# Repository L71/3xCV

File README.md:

3xCV
====

Eurorack Triple Control Voltage Adder/Attenuator/Inverter

12HP size w panel. 

** work in progress **

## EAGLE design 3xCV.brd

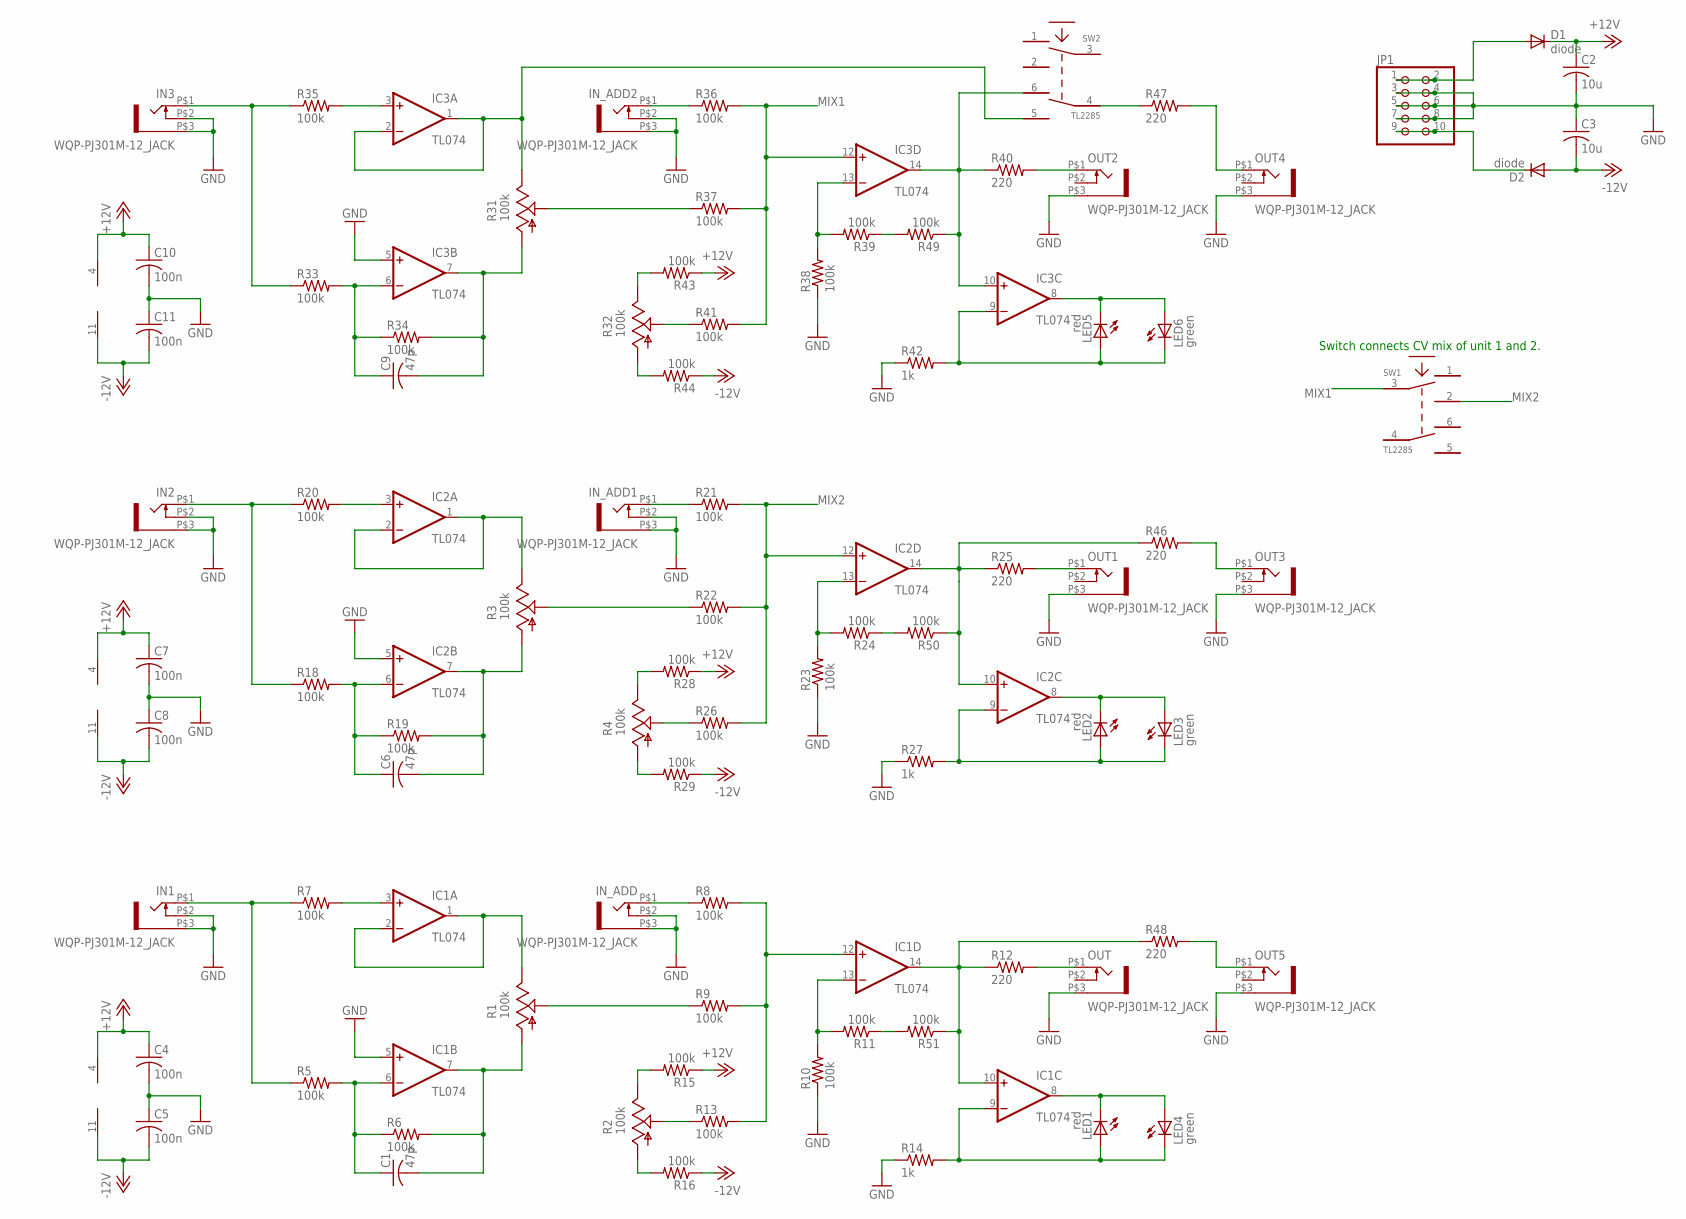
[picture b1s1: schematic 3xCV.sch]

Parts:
C1, C6, C9: 47p; C0603
C2, C3: 10u; C1206
C4, C5, C7, C8, C10, C11: 100n; C0603
D1, D2: diode; DO214AA
IC1, IC2, IC3: TL074; SO14
IN1, IN2, IN3: WQP-PJ301M-12_JACK
IN_ADD, IN_ADD1, IN_ADD2: WQP-PJ301M-12_JACK
JP1: PINHD-2X5; 2X05
LED1, LED2, LED5: red; LED3MM
LED3, LED4, LED6: green; LED3MM
OUT, OUT1, OUT2, OUT3, OUT4, OUT5: WQP-PJ301M-12_JACK
R1, R2, R3, R4, R31, R32: 100k; ALPS_POT_VERTICAL
R5, R6, R7, R8, R9, R10, R11, R13, R15, R16, R18, R19, R20, R21, R22, R23, R24, R26, R28, R29, R33, R34, R35, R36, R37, R38, R39, R41, R43, R44, R49, R50, R51: 100k; R0603
R12, R25, R40, R46, R47, R48: 220; R0603
R14, R27, R42: 1k; R0603
SW1, SW2: TL2285; TL2285_PCB

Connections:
+12V: C2.1, C4.1, C7.1, C10.1, D1.C, IC1.4 (V+), IC2.4 (V+), IC3.4 (V+), R15.1, R28.1, R43.1
-12V: C3.2, C5.2, C8.2, C11.2, D2.A, IC1.11 (V-), IC2.11 (V-), IC3.11 (V-), R16.1, R29.1, R44.1
GND: C2.2, C3.1, C4.2, C5.1, C7.2, C8.1, C10.2, C11.1, IC1.5 (+IN), IC2.5 (+IN), IC3.5 (+IN), IN1.P$2 (3), IN1.P$3 (1), IN2.P$2 (3), IN2.P$3 (1), IN3.P$2 (3), IN3.P$3 (1), IN_ADD.P$2 (3), IN_ADD.P$3 (1), IN_ADD1.P$2 (3), IN_ADD1.P$3 (1), IN_ADD2.P$2 (3), IN_ADD2.P$3 (1), JP1.3, JP1.4, JP1.5, JP1.6, JP1.7, JP1.8, OUT.P$3 (1), OUT1.P$3 (1), OUT2.P$3 (1), OUT3.P$3 (1), OUT4.P$3 (1), OUT5.P$3 (1), R10.1, R14.1, R23.1, R27.1, R38.1, R42.1
MIX1: IC3.12 (+IN), R36.2, R37.2, R41.2, SW1.3
MIX2: IC2.12 (+IN), R21.2, R22.2, R26.2, SW1.2
unnamed: IC1.9 (-IN), LED1.A, LED4.K (C), R14.2
unnamed: IN1.P$1 (2), R5.1, R7.1
unnamed: C1.1, IC1.6 (-IN), R5.2, R6.1
unnamed: IC1.3 (+IN), R7.2
unnamed: IC1.1 (OUT), IC1.2 (-IN), R1.P$1 (E)
unnamed: OUT.P$1 (2), R12.2
unnamed: C1.2, IC1.7 (OUT), R1.P$3 (A), R6.2
unnamed: R2.P$2 (S), R13.1
unnamed: R1.P$2 (S), R9.1
unnamed: IN_ADD.P$1 (2), R8.1
unnamed: IC1.8 (OUT), LED1.K (C), LED4.A
unnamed: IC1.12 (+IN), R8.2, R9.2, R13.2
unnamed: IC1.10 (+IN), IC1.14 (OUT), R12.1, R48.1, R51.1
unnamed: IC1.13 (-IN), R10.2, R11.2
unnamed: R2.P$1 (E), R15.2
unnamed: R2.P$3 (A), R16.2
unnamed: D2.C, JP1.9, JP1.10
unnamed: R47.1, SW2.4
unnamed: OUT3.P$1 (2), R46.2
unnamed: D1.A, JP1.1, JP1.2
unnamed: OUT4.P$1 (2), R47.2
unnamed: IN2.P$1 (2), R18.1, R20.1
unnamed: C6.1, IC2.6 (-IN), R18.2, R19.1
unnamed: IC2.3 (+IN), R20.2
unnamed: IC2.1 (OUT), IC2.2 (-IN), R3.P$1 (E)
unnamed: C6.2, IC2.7 (OUT), R3.P$3 (A), R19.2
unnamed: R3.P$2 (S), R22.1
unnamed: IN_ADD1.P$1 (2), R21.1
unnamed: IC2.13 (-IN), R23.2, R24.2
unnamed: OUT1.P$1 (2), R25.2
unnamed: R4.P$2 (S), R26.1
unnamed: IC2.9 (-IN), LED2.A, LED3.K (C), R27.2
unnamed: IC2.8 (OUT), LED2.K (C), LED3.A
unnamed: R4.P$1 (E), R28.2
unnamed: R4.P$3 (A), R29.2
unnamed: IN3.P$1 (2), R33.1, R35.1
unnamed: C9.1, IC3.6 (-IN), R33.2, R34.1
unnamed: IC3.3 (+IN), R35.2
unnamed: IC3.1 (OUT), IC3.2 (-IN), R31.P$1 (E), SW2.5
unnamed: C9.2, IC3.7 (OUT), R31.P$3 (A), R34.2
unnamed: R31.P$2 (S), R37.1
unnamed: IN_ADD2.P$1 (2), R36.1
unnamed: IC3.10 (+IN), IC3.14 (OUT), R40.1, R49.1, SW2.6
unnamed: IC3.13 (-IN), R38.2, R39.2
unnamed: OUT2.P$1 (2), R40.2
unnamed: R32.P$2 (S), R41.1
unnamed: IC3.9 (-IN), LED5.A, LED6.K (C), R42.2
unnamed: IC3.8 (OUT), LED5.K (C), LED6.A
unnamed: R32.P$1 (E), R43.2
unnamed: R32.P$3 (A), R44.2
unnamed: OUT5.P$1 (2), R48.2
unnamed: IC2.10 (+IN), IC2.14 (OUT), R25.1, R46.1, R50.1
unnamed: R11.1, R51.2
unnamed: R24.1, R50.2
unnamed: R39.1, R49.2

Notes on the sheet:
Switch connects CV mix of unit 1 and 2.

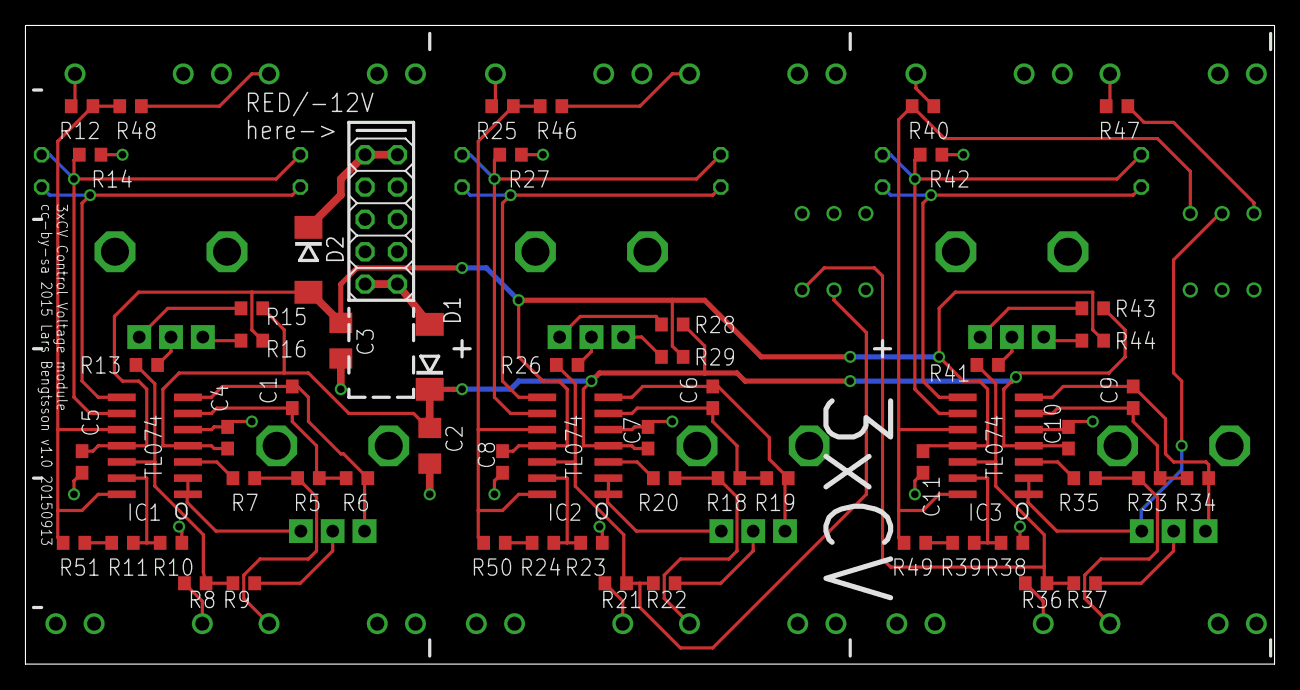
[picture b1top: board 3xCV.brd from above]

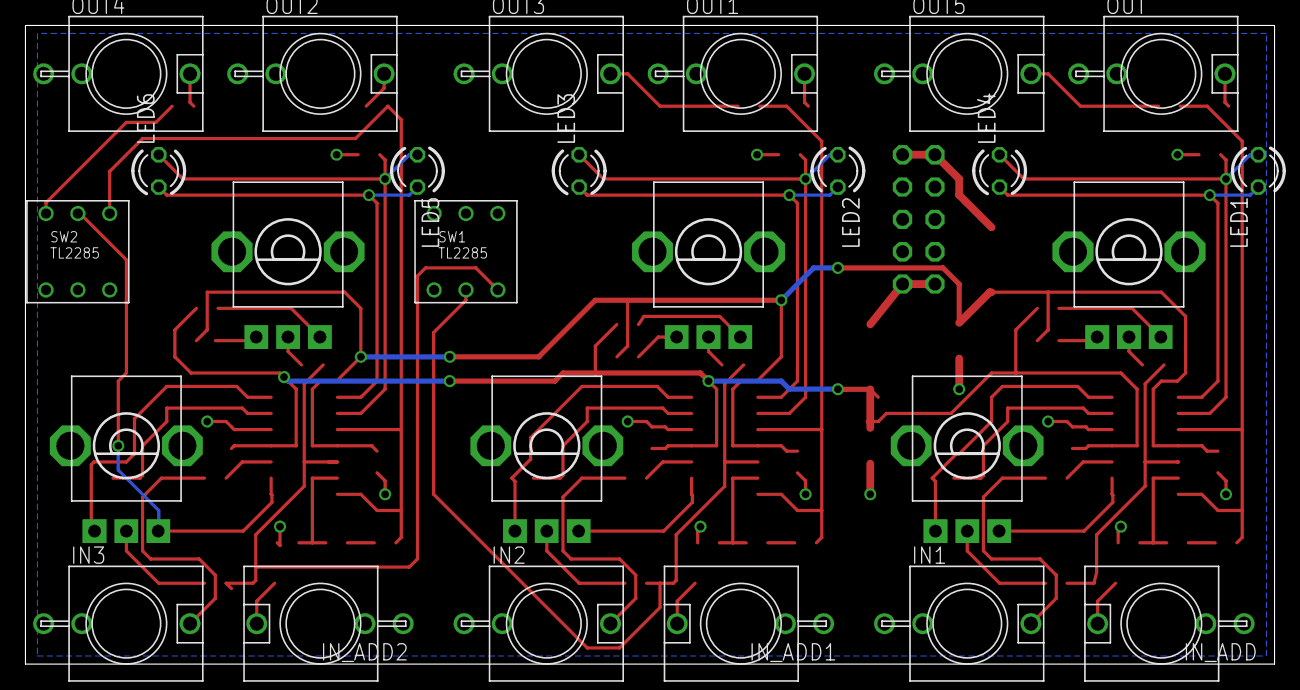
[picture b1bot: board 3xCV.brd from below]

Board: 2 copper layers, 98.1 x 50.2 mm, 85 parts (26 on the bottom side), 60 nets.

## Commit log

2015-09-09 Initial commit.
2015-09-12 initial add of v1.0 board and schematics
2015-09-13 Somewhat modified. No thru jacks (out of space). Aligned input jacks with outputs.
2015-09-13 Initial add of halfway-finished panel.
2015-09-13 Added back 1+2 mix button. There is room for it. Yay! =)
2015-09-13 Initial design completed (methinks :) ).
2015-09-13 Moved copyright label a bit.
2015-09-13 Moved dimensional markers onto board (were outside board outline before)
2015-09-13 Added thru switch in unit 1, can switch output 1 to provide buffered output of unchanged input signal.
2015-09-13 Moved labels around a bit.
2015-09-14 Minor routing adjustments/optimized traces
2015-09-14 initial add of readme file.
2015-09-19 Moved resistors around output of unit 2, moved a few other labels.
2015-09-19 Split panel outline into separate lines. Adjustment to "knob arcs".
2015-09-19 Fixed line fill issues. (unspecified fill does not play well with Ponoko, must be set to "none".)
2016-01-11 Adjusted panel bottom edge and holes downwards 1/40" to better fit racks w 3mm screws.

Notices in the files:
3xCV.brd:
cc-by-sa 2015 Lars Bengtsson v1.0 20150913
